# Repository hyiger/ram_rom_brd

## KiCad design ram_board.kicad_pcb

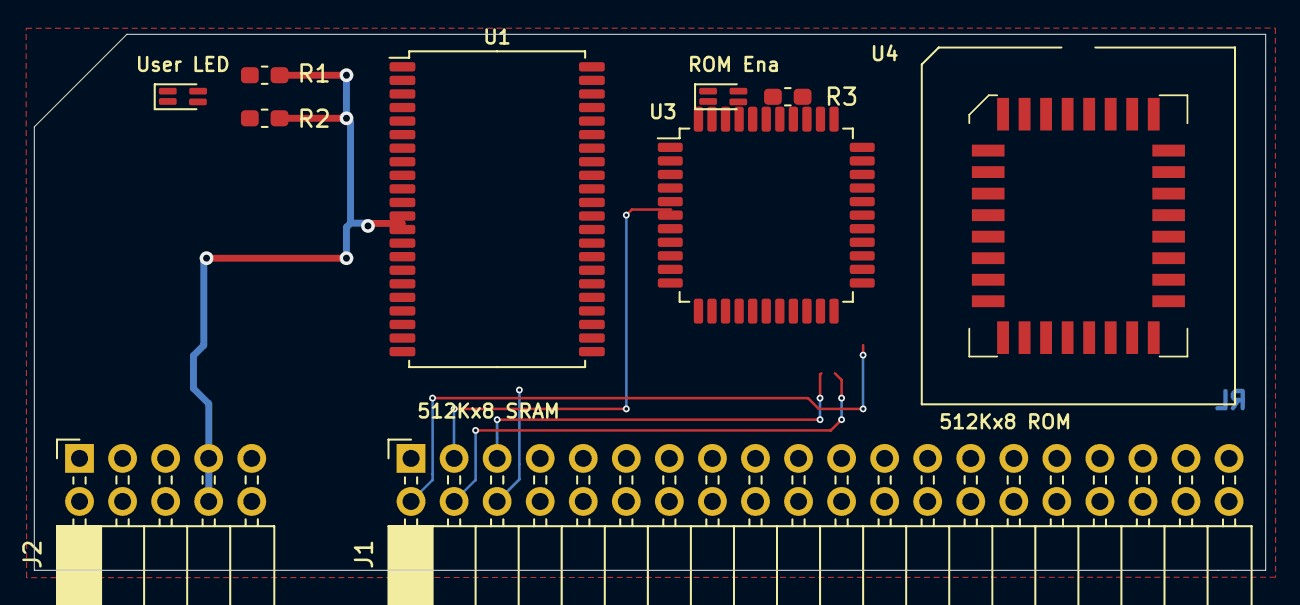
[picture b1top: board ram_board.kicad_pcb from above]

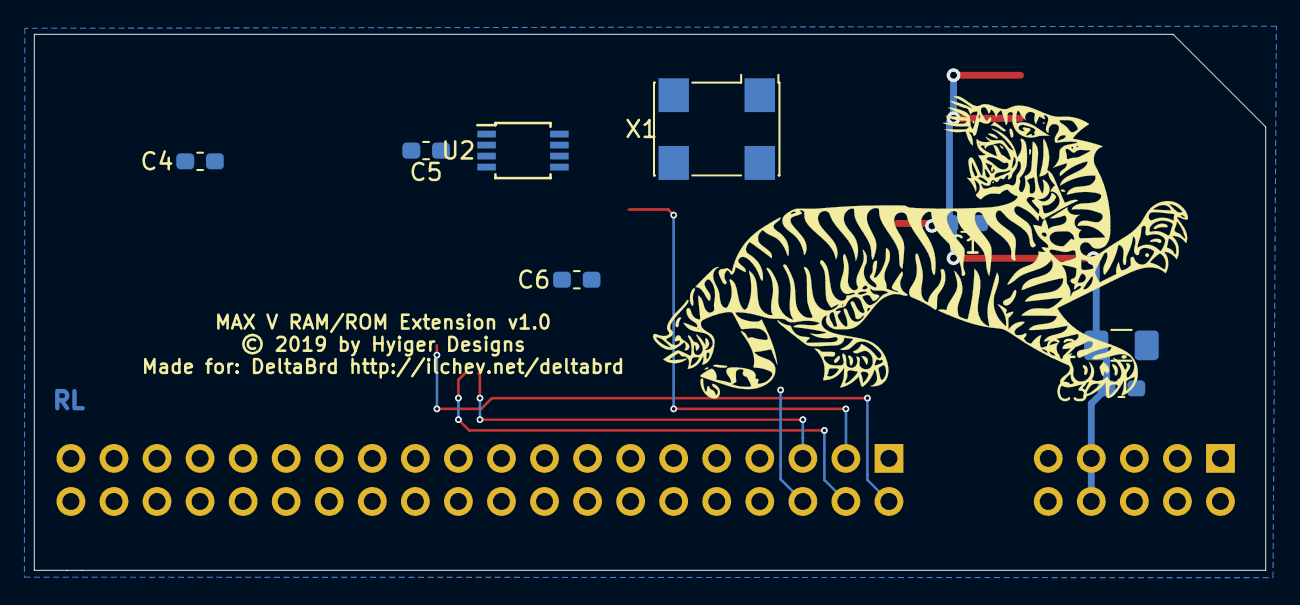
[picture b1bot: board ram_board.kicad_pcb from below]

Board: 2 copper layers, 72.6 x 31.6 mm, 18 parts (8 on the bottom side), 48 nets.

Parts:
C1, C3, C4, C5, C6: 100nF; C_0603_1608Metric_Pad1.05x0.95mm_HandSolder
C2: 100uF; C_1206_3216Metric_Pad1.42x1.75mm_HandSolder
D1, D2: LED; LED_2C_0603_1608Metric_Pad1.05x0.95mm_HandSolder
J1: Bus; PinSocket_2x20_P2.54mm_Horizontal
J2: PWR; PinSocket_2x05_P2.54mm_Horizontal
R1, R2, R3: 360R; R_0603_1608Metric_Pad1.05x0.95mm_HandSolder
U1: IS61C5128AL-10TLI; TSOP-II-44_10.16x18.41mm_P0.8mm
U2: 74LVC2G240; TSSOP-8_3x3mm_P0.65mm
U3: CPU - Z84C0010AEG; LQFP-44_10x10mm_P0.8mm
U4: SST39VF040-70-4C-NHE; PLCC-32_SMD-Socket
X1: ASV-20MHz; Oscillator_SMD_Abracon_ASV-4Pin_7.0x5.1mm

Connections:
/1V8: J2.5, J2.6
/5V: J2.9, J2.10
/A0: J1.7, U1.3, U3.27, U4.12
/A1: J1.10, U1.4, U3.28, U4.11
/A2: J1.9, U1.5, U3.29, U4.10
/A3: J1.12, U1.6, U3.30, U4.9
/A4: J1.11, U1.7, U3.31, U4.8
/A5: J1.14, U1.16, U3.32, U4.7
/A6: J1.13, U1.17, U3.34, U4.6
/A7: J1.16, U1.18, U3.35, U4.5
/A8: J1.15, U1.19, U3.36, U4.27
/A9: J1.18, U1.20, U3.37, U4.26
/A10: J1.17, U1.26, U3.38, U4.23
/A11: J1.20, U1.27, U3.40, U4.25
/A12: J1.19, U1.28, U3.41, U4.4
/A13: J1.22, U1.29, U3.42, U4.28
/A14: J1.21, U1.30, U3.43, U4.29
/A15: J1.24, U1.38, U3.44, U4.3
/A16: J1.23, U1.39, U4.2
/A17: J1.26, U1.40, U4.30
/A18: J1.25, U1.41, U4.1
/CLK: J1.3, U3.1, X1.3
/D0: J1.33, U1.9, U3.9, U4.13
/D1: J1.34, U1.10, U3.10, U4.14
/D2: J1.35, U1.13, U3.7, U4.15
/D3: J1.36, U1.14, U3.3, U4.17
/D4: J1.37, U1.31, U3.2, U4.18
/D5: J1.38, U1.32, U3.4, U4.19
/D6: J1.39, U1.35, U3.5, U4.20
/D7: J1.40, U1.36, U3.8, U4.21
/LED_G: D1.4, J1.28
/LED_R: D1.2, J1.27
/~BUSREQ: J1.4, U3.22
/~ENA: J1.29, U2.1, U2.7
/~IORQ: J1.6, U3.16
/~MREQ: J1.8, U3.15
/~RAM: J1.30, U1.8, U2.2
/~RD: J1.31, U1.37, U3.18, U4.24
/~RESET: J1.2, U3.23
/~ROM: D2.2, U2.5, U2.6, U4.22
/~WAIT: J1.5, U3.21
/~WR: J1.32, U1.15, U3.19, U4.31
GND: C1.2, C2.2, C3.2, C4.2, C5.2, C6.2, J1.1, J2.1, J2.2, J2.3, J2.4, U1.12, U1.34, U2.4, U3.26, U4.16, X1.2
unnamed: D1.1, R1.1
unnamed: D1.3, R2.1
unnamed: D2.1, D2.3, R3.1
unnamed: D2.4, U2.3
VCC: C1.1, C2.1, C3.1, C4.1, C5.1, C6.1, J2.7, J2.8, R1.2, R2.2, R3.2, U1.11, U1.33, U2.8, U3.6, U4.32, X1.1, X1.4

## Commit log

2019-07-02 initial version
2019-07-03 Wiring up
2019-07-03 more cowbell
2019-07-03 finished routing, gerbers
2019-07-03 Labeling and status leds
2019-07-03 Final Version
2019-07-04 added BOM and schema docs
2019-07-04 ignore mac
2019-07-05 fixed leds, spacing
2019-07-08 gnd plane stitching
2019-07-09 added switch, switch to 4 layer brd
2019-07-09 fixed labeling
2019-07-09 redesign
2019-07-10 tri-state led driver
2019-07-10 switched to discrete resistors,
2019-07-11 simplified pins, finished routing
2019-07-20 fixed up LED's and muxed signals
2019-07-26 added z80
2019-07-26 added glue logic code for deltabrd
2019-07-26 added clock divider, switched to proper CPLD
2019-07-27 setup testbench
2019-07-27 bug fix
2019-07-27 xxxx
2019-07-27 fixed testbench, added clocks that work with modelsim
2019-07-27 option to remove uart, organized tests
2019-07-27 synchronous model
2019-07-27 formatting and cleanup
2019-07-30 re-gridded
2019-08-02 Added i2c master
2019-08-06 Added plcc socket to library

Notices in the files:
ram_board.kicad_pcb:
© 2019 by Hyiger Designs
